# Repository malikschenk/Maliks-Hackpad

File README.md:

# My Hackpad

## Overview
My hackpad features 8 keys, two rotary encoders and an OLED Display.  
**Work in Progress:** I'll submited the project and build my Hackpad as soon as possible.  
Check my progress on [Stardance](https://stardance.hackclub.com/projects/44913)!

## Features
- 8x MX Switches
- 1x 128x32 OLED Display
- 2x EC11 Rotary Encoders
  
Because I don't have enough pins, just one of the two rotary encoders can send a rotary signal. But you can at least press both of them!

## PCB
I designed my PCB inside KiCad. The libraries I used were from the Hackpad website.

### Schematic

<br>
<br>

### PCB

<br>
<br>

### PCB in 3d

<br>
<br>

## Case

The case consists of the top and bottom plate. The two plates are held together using four M3 screws and four heat-set inserts. The  encoder knobs are based on the [Hack Club knob design](https://github.com/hackclub/hackpad?tab=readme-ov-file). The color scheme is inspired by Teenage Engineering designs.

## Firmware
The firmware runs on CircuitPython using the KMK fromework. To set it up you need to do this few things:
- Install CircuitPython on your XIAO
- Download the KMK framework and put into the lib folder
- Download the Adafruit CircuitPython Bundle and add `adafruit_displayio_ssd1306` and `adafruit_display_text` to lib
- Upload the code.py file and the lib folder to the root
<br>

It should look like this:
```
CIRCUITPY
├─── code.py
└─── lib/
   ├─── kmk/
   ├─── adafruit_display_text/
   └─── adafruit_displayio_ssd1306/
```

## BOM

| Comment | Designator | Footprint | Quantity |
| :--- | :--- | :--- | :--- |
| Seeed XIAO RP2040 | U1 | XIAO_RP2040 | 1 |
| MX Switch | SW1-SW8 | Button_Switch_Keyboard:SW_KEY_MX | 8 |
| EC11 Rotary Encoder | RE1-RE2 | RotaryEncoder_Switch | 2 |
| 0.91 inch OLED Display | U2 | OLED_128x32 | 1 |
| 1N4148 Diode | D2-D11 | Diode_SMD:D_SOD-123 | 10 |
| M3 Heat-Set Insert | H1-H4 | Hardware | 4 |
| M3x12mm Screw | S1-S4 | Hardware | 4 |

## Next Steps
- Build my Hackpad
<br>
  
It was really fun to make this project and I learned a lot of things. Thanks to Hackclub!
<br>

### Stay tuned for updates!

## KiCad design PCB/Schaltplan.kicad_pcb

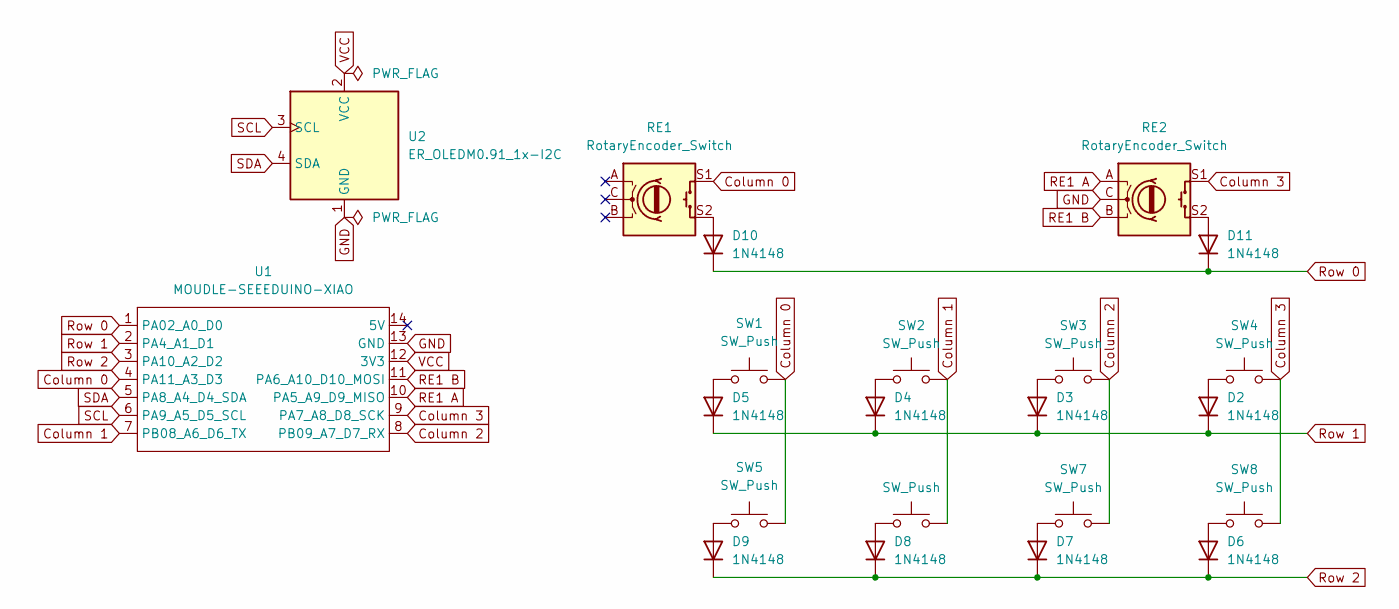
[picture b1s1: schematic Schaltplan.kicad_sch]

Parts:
D2, D3, D4, D5, D6, D7, D8, D9, D10, D11: 1N4148; D_DO-35_SOD27_P7.62mm_Horizontal
RE1, RE2: RotaryEncoder_Switch; RotaryEncoder_Alps_EC11E-Switch_Vertical_H20mm
SW1, SW2, SW3, SW4, SW5, SW6, SW7, SW8: SW_Push; SW_Cherry_MX_1.00u_PCB
U1: MOUDLE-SEEEDUINO-XIAO; XIAO-Generic-Hybrid-14P-2.54-21X17.8MM
U2: ER_OLEDM0.91_1x-I2C

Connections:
Column 0: RE1.S1, SW1.2, SW5.2, U1.4 (PA11_A3_D3)
Column 1: SW2.2, SW6.2, U1.7 (PB08_A6_D6_TX)
Column 2: SW3.2, SW7.2, U1.8 (PB09_A7_D7_RX)
Column 3: RE2.S1, SW4.2, SW8.2, U1.9 (PA7_A8_D8_SCK)
GND: RE2.C, U1.13 (GND), U2.1 (GND)
unnamed: D2.2 (A), SW4.1
unnamed: D3.2 (A), SW3.1
unnamed: D4.2 (A), SW2.1
unnamed: D5.2 (A), SW1.1
unnamed: D6.2 (A), SW8.1
unnamed: D7.2 (A), SW7.1
unnamed: D8.2 (A), SW6.1
unnamed: D9.2 (A), SW5.1
unnamed: D10.2 (A), RE1.S2
unnamed: D11.2 (A), RE2.S2
RE1 A: RE2.A, U1.10 (PA5_A9_D9_MISO)
RE1 B: RE2.B, U1.11 (PA6_A10_D10_MOSI)
Row 0: D10.1 (K), D11.1 (K), U1.1 (PA02_A0_D0)
Row 1: D2.1 (K), D3.1 (K), D4.1 (K), D5.1 (K), U1.2 (PA4_A1_D1)
Row 2: D6.1 (K), D7.1 (K), D8.1 (K), D9.1 (K), U1.3 (PA10_A2_D2)
SCL: U1.6 (PA9_A5_D5_SCL), U2.3 (SCL)
SDA: U1.5 (PA8_A4_D4_SDA), U2.4 (SDA)
VCC: U1.12 (3V3), U2.2 (VCC)

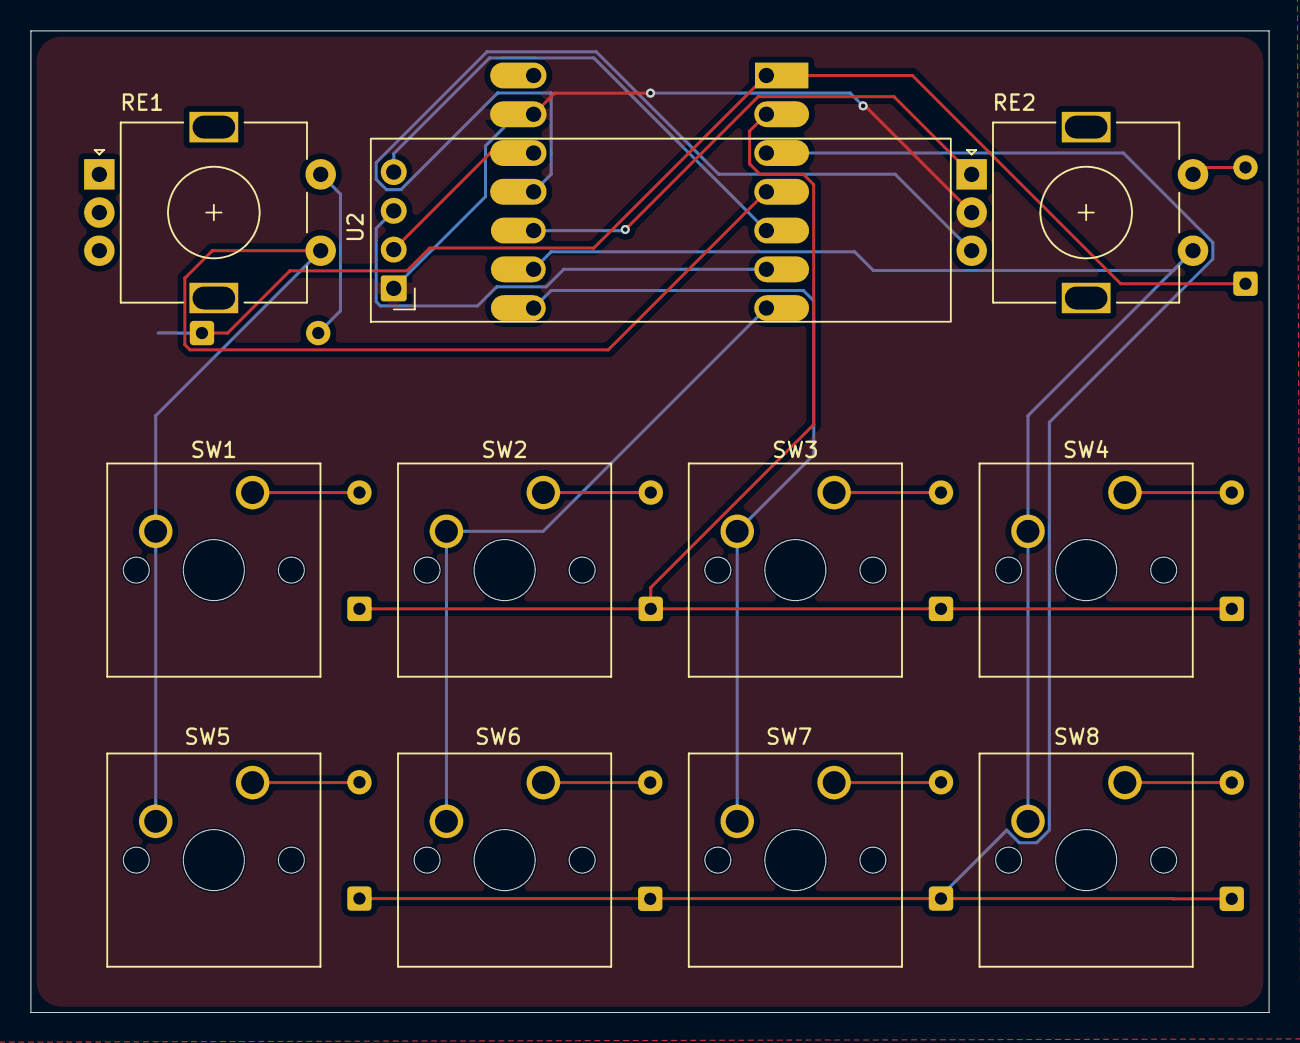
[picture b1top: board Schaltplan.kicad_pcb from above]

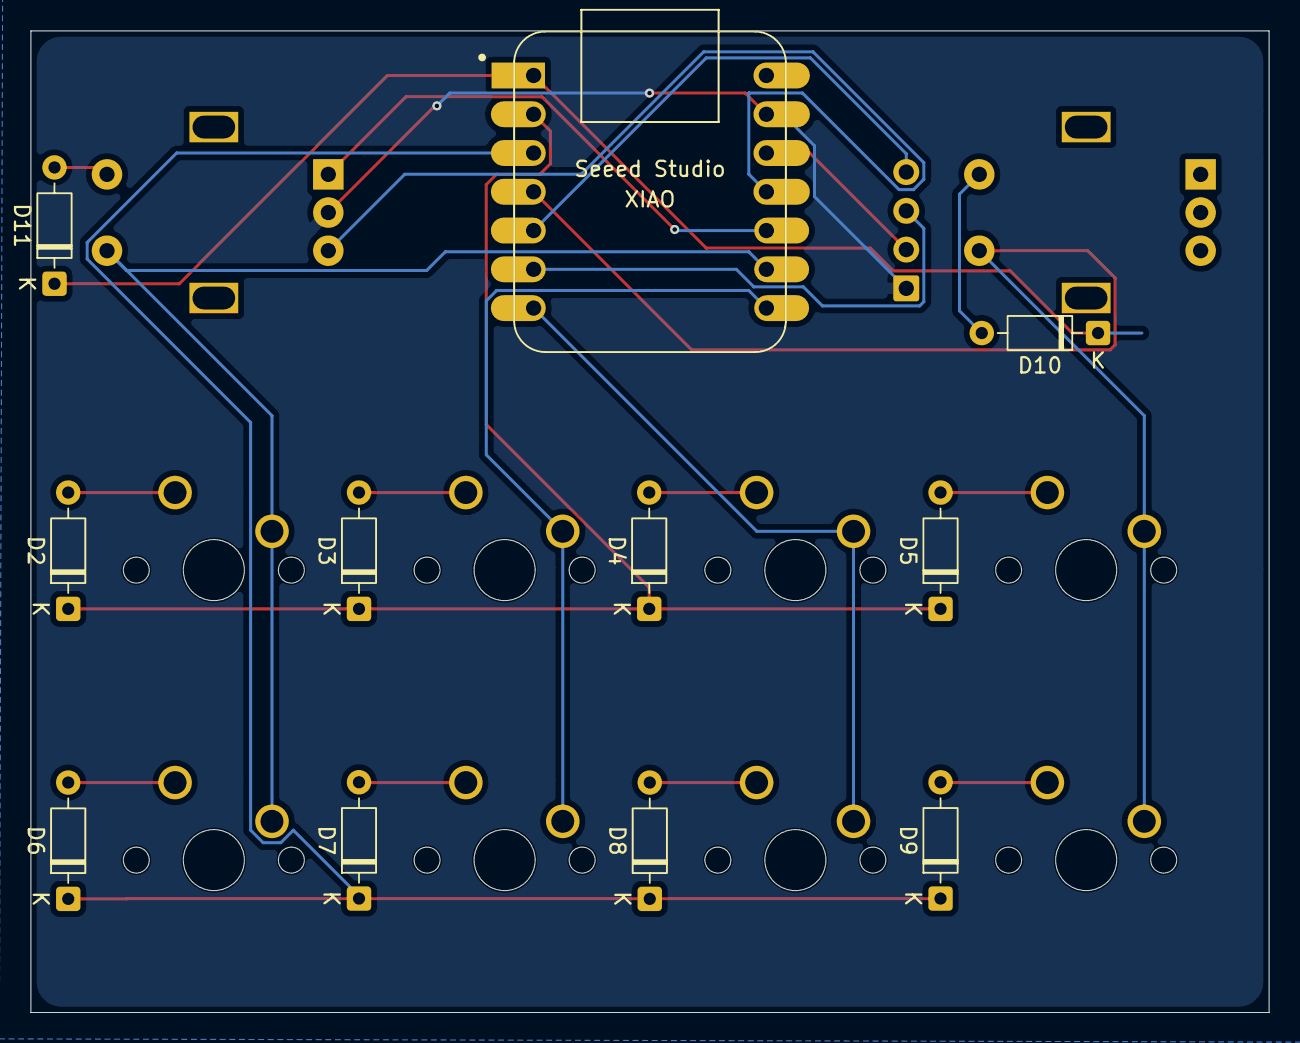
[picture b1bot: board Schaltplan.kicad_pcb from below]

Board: 2 copper layers, 81.1 x 64.3 mm, 22 parts (11 on the bottom side), 23 nets.
